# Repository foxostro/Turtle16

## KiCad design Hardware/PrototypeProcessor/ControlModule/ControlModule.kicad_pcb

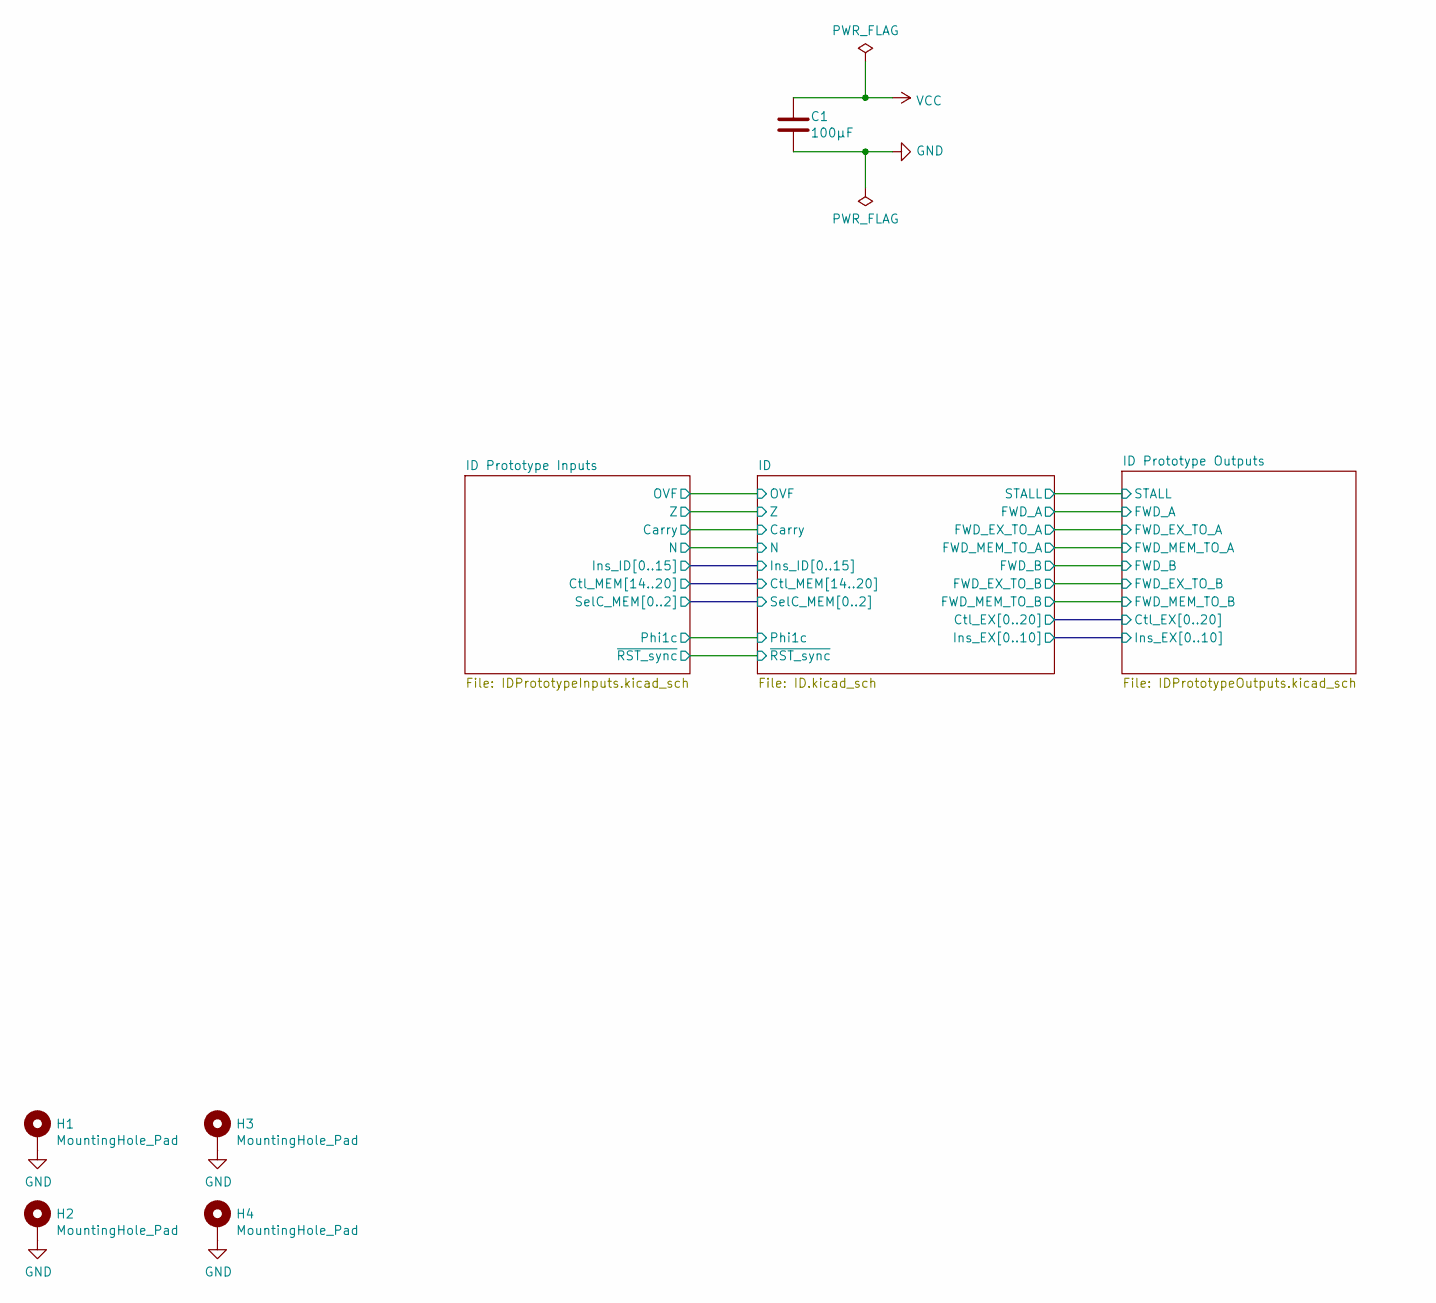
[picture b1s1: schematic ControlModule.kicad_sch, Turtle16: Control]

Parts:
C1: 100µF; C_1206_3216Metric_Pad1.33x1.80mm_HandSolder
H1, H2, H3, H4: MountingHole_Pad; MountingHole_3.2mm_M3_Pad

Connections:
GND: C1.2, H1.1, H2.1, H3.1, H4.1; also elsewhere on the board
VCC: C1.1; also elsewhere on the board

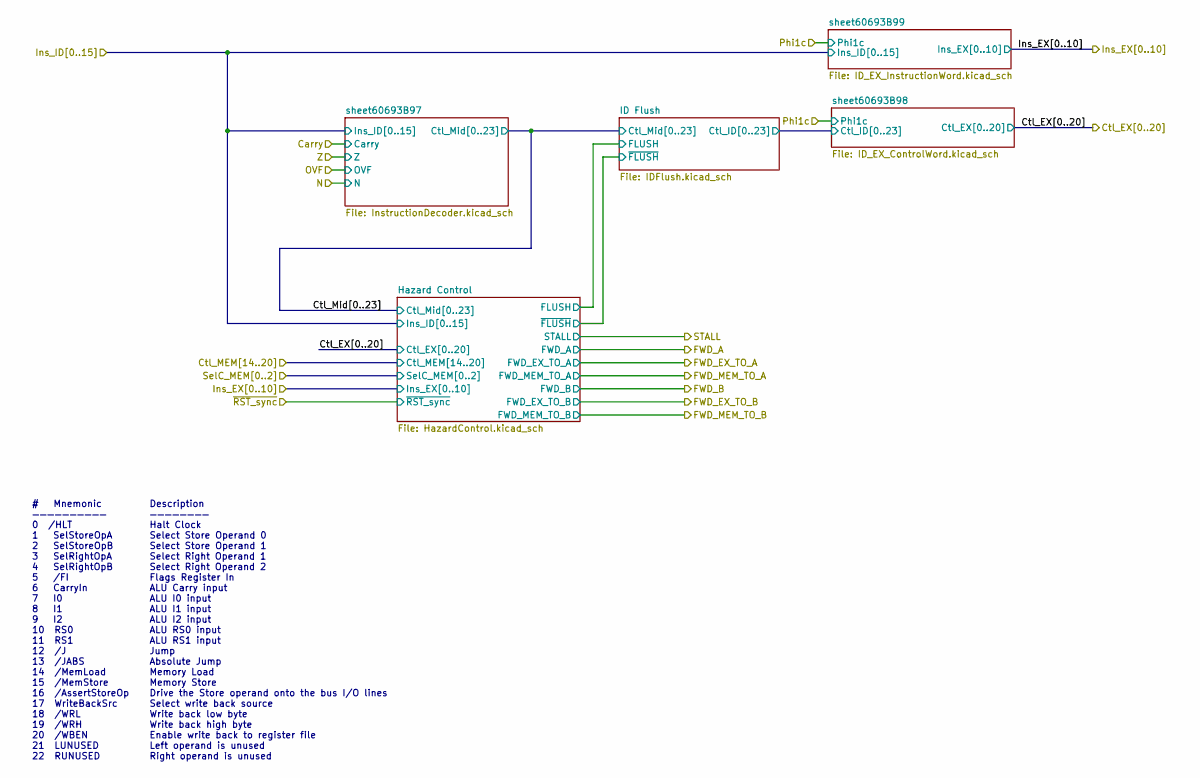
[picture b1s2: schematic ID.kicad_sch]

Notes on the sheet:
Description ———————— Halt Clock Select Store Operand 0 Select Store Operand 1 Select Right Operand 1 Select Right Operand 2 Flags Register In ALU Carry input ALU I0 input ALU I1 input ALU I2 input ALU RS0 input ALU RS1 input Jump Absolute Jump Memory Load Memory Store Drive the Store operand onto t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
# Mnemonic —————————— 0 /HLT 1 SelStoreOpA 2 SelStoreOpB 3 SelRightOpA 4 SelRightOpB 5 /FI 6 CarryIn 7 I0 8 I1 9 I2 10 RS0 11 RS1 12 /J 13 /JABS 14 /MemLoad 15 /MemStore 16 /AssertStoreOp 17 WriteBackSrc 18 /WRL 19 /WRH 20 /WBEN 21 LUNUSED 22 RUNUSED

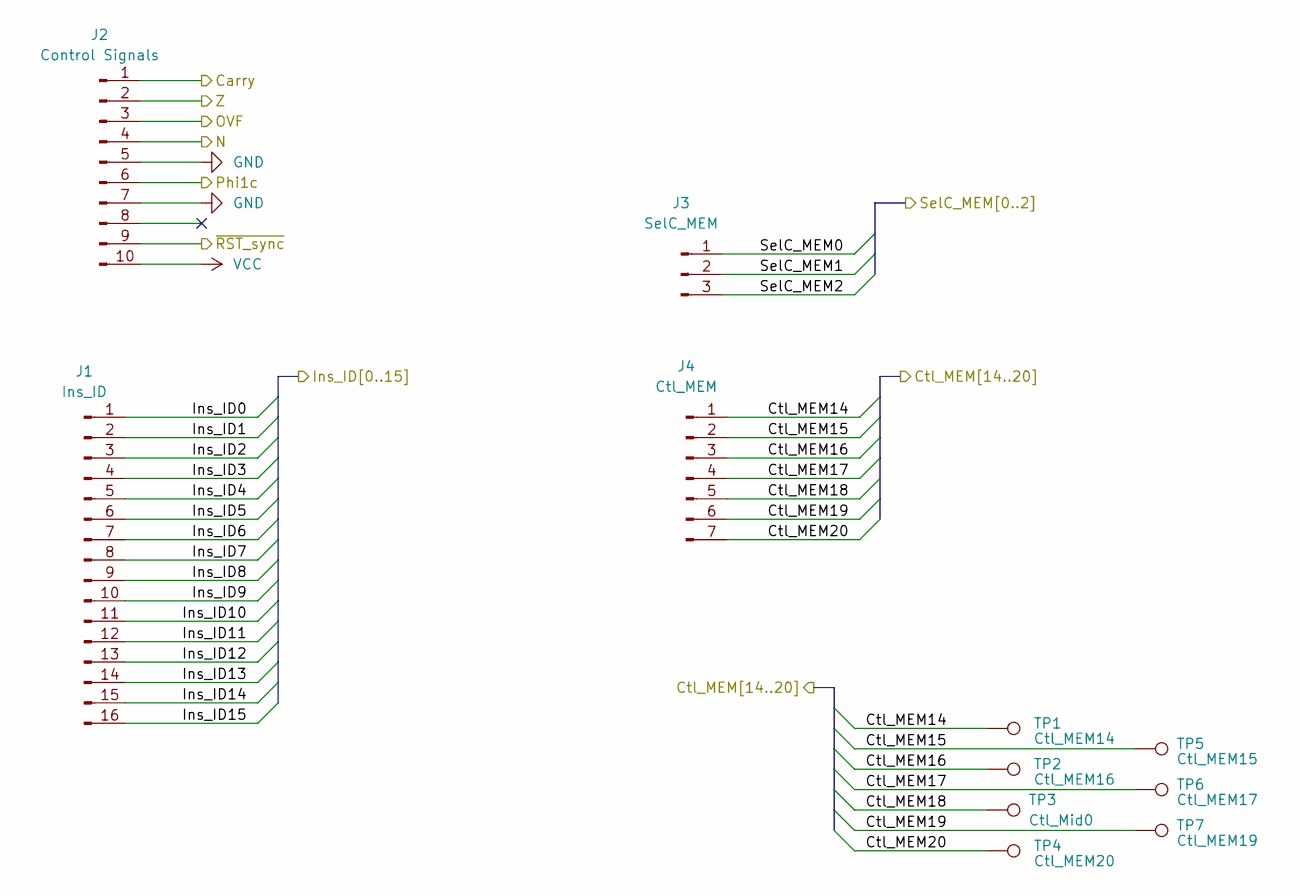
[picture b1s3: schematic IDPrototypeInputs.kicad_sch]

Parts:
J1: Ins_ID; PinHeader_1x16_P2.54mm_Vertical
J2: Control Signals; PinHeader_1x10_P2.54mm_Vertical
J3: SelC_MEM; PinHeader_1x03_P2.54mm_Vertical
J4: Ctl_MEM; PinHeader_1x07_P2.54mm_Vertical
TP1: Ctl_MEM14; TestPoint_Pad_D1.0mm
TP2: Ctl_MEM16; TestPoint_Pad_D1.0mm
TP3: Ctl_Mid0; TestPoint_Pad_D1.0mm
TP4: Ctl_MEM20; TestPoint_Pad_D1.0mm
TP5: Ctl_MEM15; TestPoint_Pad_D1.0mm
TP6: Ctl_MEM17; TestPoint_Pad_D1.0mm
TP7: Ctl_MEM19; TestPoint_Pad_D1.0mm

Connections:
/ID Prototype Inputs/Carry: J2.1; also elsewhere on the board
/ID Prototype Inputs/Ctl_MEM14: J4.1, TP1.1
/ID Prototype Inputs/Ctl_MEM15: J4.2, TP5.1
/ID Prototype Inputs/Ctl_MEM16: J4.3, TP2.1
/ID Prototype Inputs/Ctl_MEM17: J4.4, TP6.1; also elsewhere on the board
/ID Prototype Inputs/Ctl_MEM18: J4.5, TP3.1
/ID Prototype Inputs/Ctl_MEM19: J4.6, TP7.1
/ID Prototype Inputs/Ctl_MEM20: J4.7, TP4.1; also elsewhere on the board
/ID Prototype Inputs/Ins_ID0: J1.1; also elsewhere on the board
/ID Prototype Inputs/Ins_ID1: J1.2; also elsewhere on the board
/ID Prototype Inputs/Ins_ID2: J1.3; also elsewhere on the board
/ID Prototype Inputs/Ins_ID3: J1.4; also elsewhere on the board
/ID Prototype Inputs/Ins_ID4: J1.5; also elsewhere on the board
/ID Prototype Inputs/Ins_ID5: J1.6; also elsewhere on the board
/ID Prototype Inputs/Ins_ID6: J1.7; also elsewhere on the board
/ID Prototype Inputs/Ins_ID7: J1.8; also elsewhere on the board
/ID Prototype Inputs/Ins_ID8: J1.9; also elsewhere on the board
/ID Prototype Inputs/Ins_ID9: J1.10; also elsewhere on the board
/ID Prototype Inputs/Ins_ID10: J1.11; also elsewhere on the board
/ID Prototype Inputs/Ins_ID11: J1.12; also elsewhere on the board
/ID Prototype Inputs/Ins_ID12: J1.13; also elsewhere on the board
/ID Prototype Inputs/Ins_ID13: J1.14; also elsewhere on the board
/ID Prototype Inputs/Ins_ID14: J1.15; also elsewhere on the board
/ID Prototype Inputs/Ins_ID15: J1.16; also elsewhere on the board
/ID Prototype Inputs/N: J2.4; also elsewhere on the board
/ID Prototype Inputs/OVF: J2.3; also elsewhere on the board
/ID Prototype Inputs/Phi1c: J2.6; also elsewhere on the board
/ID Prototype Inputs/SelC_MEM0: J3.1; also elsewhere on the board
/ID Prototype Inputs/SelC_MEM1: J3.2; also elsewhere on the board
/ID Prototype Inputs/SelC_MEM2: J3.3; also elsewhere on the board
/ID Prototype Inputs/Z: J2.2; also elsewhere on the board
/ID Prototype Inputs/~RST_sync: J2.9; also elsewhere on the board
GND: J2.5, J2.7; also elsewhere on the board
VCC: J2.10; also elsewhere on the board

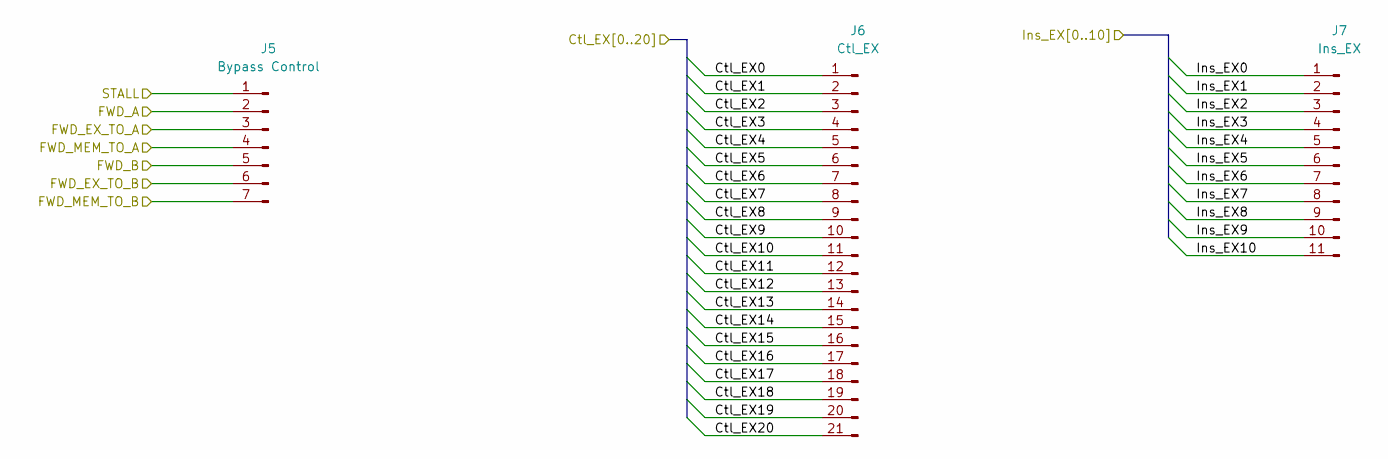
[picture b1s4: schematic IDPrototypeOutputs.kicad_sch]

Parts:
J5: Bypass Control; PinHeader_1x07_P2.54mm_Vertical
J6: Ctl_EX; PinHeader_1x21_P2.54mm_Vertical
J7: Ins_EX; PinHeader_1x11_P2.54mm_Vertical

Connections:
/ID Prototype Outputs/FWD_A: J5.2; also elsewhere on the board
/ID Prototype Outputs/FWD_B: J5.5; also elsewhere on the board
/ID Prototype Outputs/FWD_EX_TO_A: J5.3; also elsewhere on the board
/ID Prototype Outputs/FWD_EX_TO_B: J5.6; also elsewhere on the board
/ID Prototype Outputs/FWD_MEM_TO_A: J5.4; also elsewhere on the board
/ID Prototype Outputs/FWD_MEM_TO_B: J5.7; also elsewhere on the board
/ID Prototype Outputs/Ins_EX0: J7.1; also elsewhere on the board
/ID Prototype Outputs/Ins_EX1: J7.2; also elsewhere on the board
/ID Prototype Outputs/Ins_EX2: J7.3; also elsewhere on the board
/ID Prototype Outputs/Ins_EX3: J7.4; also elsewhere on the board
/ID Prototype Outputs/Ins_EX4: J7.5; also elsewhere on the board
/ID Prototype Outputs/Ins_EX5: J7.6; also elsewhere on the board
/ID Prototype Outputs/Ins_EX6: J7.7; also elsewhere on the board
/ID Prototype Outputs/Ins_EX7: J7.8; also elsewhere on the board
/ID Prototype Outputs/Ins_EX8: J7.9; also elsewhere on the board
/ID Prototype Outputs/Ins_EX9: J7.10; also elsewhere on the board
/ID Prototype Outputs/Ins_EX10: J7.11; also elsewhere on the board
/ID/Ctl_EX0: J6.1; also elsewhere on the board
/ID/Ctl_EX1: J6.2; also elsewhere on the board
/ID/Ctl_EX2: J6.3; also elsewhere on the board
/ID/Ctl_EX3: J6.4; also elsewhere on the board
/ID/Ctl_EX4: J6.5; also elsewhere on the board
/ID/Ctl_EX5: J6.6; also elsewhere on the board
/ID/Ctl_EX6: J6.7; also elsewhere on the board
/ID/Ctl_EX7: J6.8; also elsewhere on the board
/ID/Ctl_EX8: J6.9; also elsewhere on the board
/ID/Ctl_EX9: J6.10; also elsewhere on the board
/ID/Ctl_EX10: J6.11; also elsewhere on the board
/ID/Ctl_EX11: J6.12; also elsewhere on the board
/ID/Ctl_EX12: J6.13; also elsewhere on the board
/ID/Ctl_EX13: J6.14; also elsewhere on the board
/ID/Ctl_EX14: J6.15; also elsewhere on the board
/ID/Ctl_EX15: J6.16; also elsewhere on the board
/ID/Ctl_EX16: J6.17; also elsewhere on the board
/ID/Ctl_EX17: J6.18; also elsewhere on the board
/ID/Ctl_EX18: J6.19; also elsewhere on the board
/ID/Ctl_EX19: J6.20; also elsewhere on the board
/ID/Ctl_EX20: J6.21; also elsewhere on the board
/ID/Hazard Control/STALL: J5.1; also elsewhere on the board

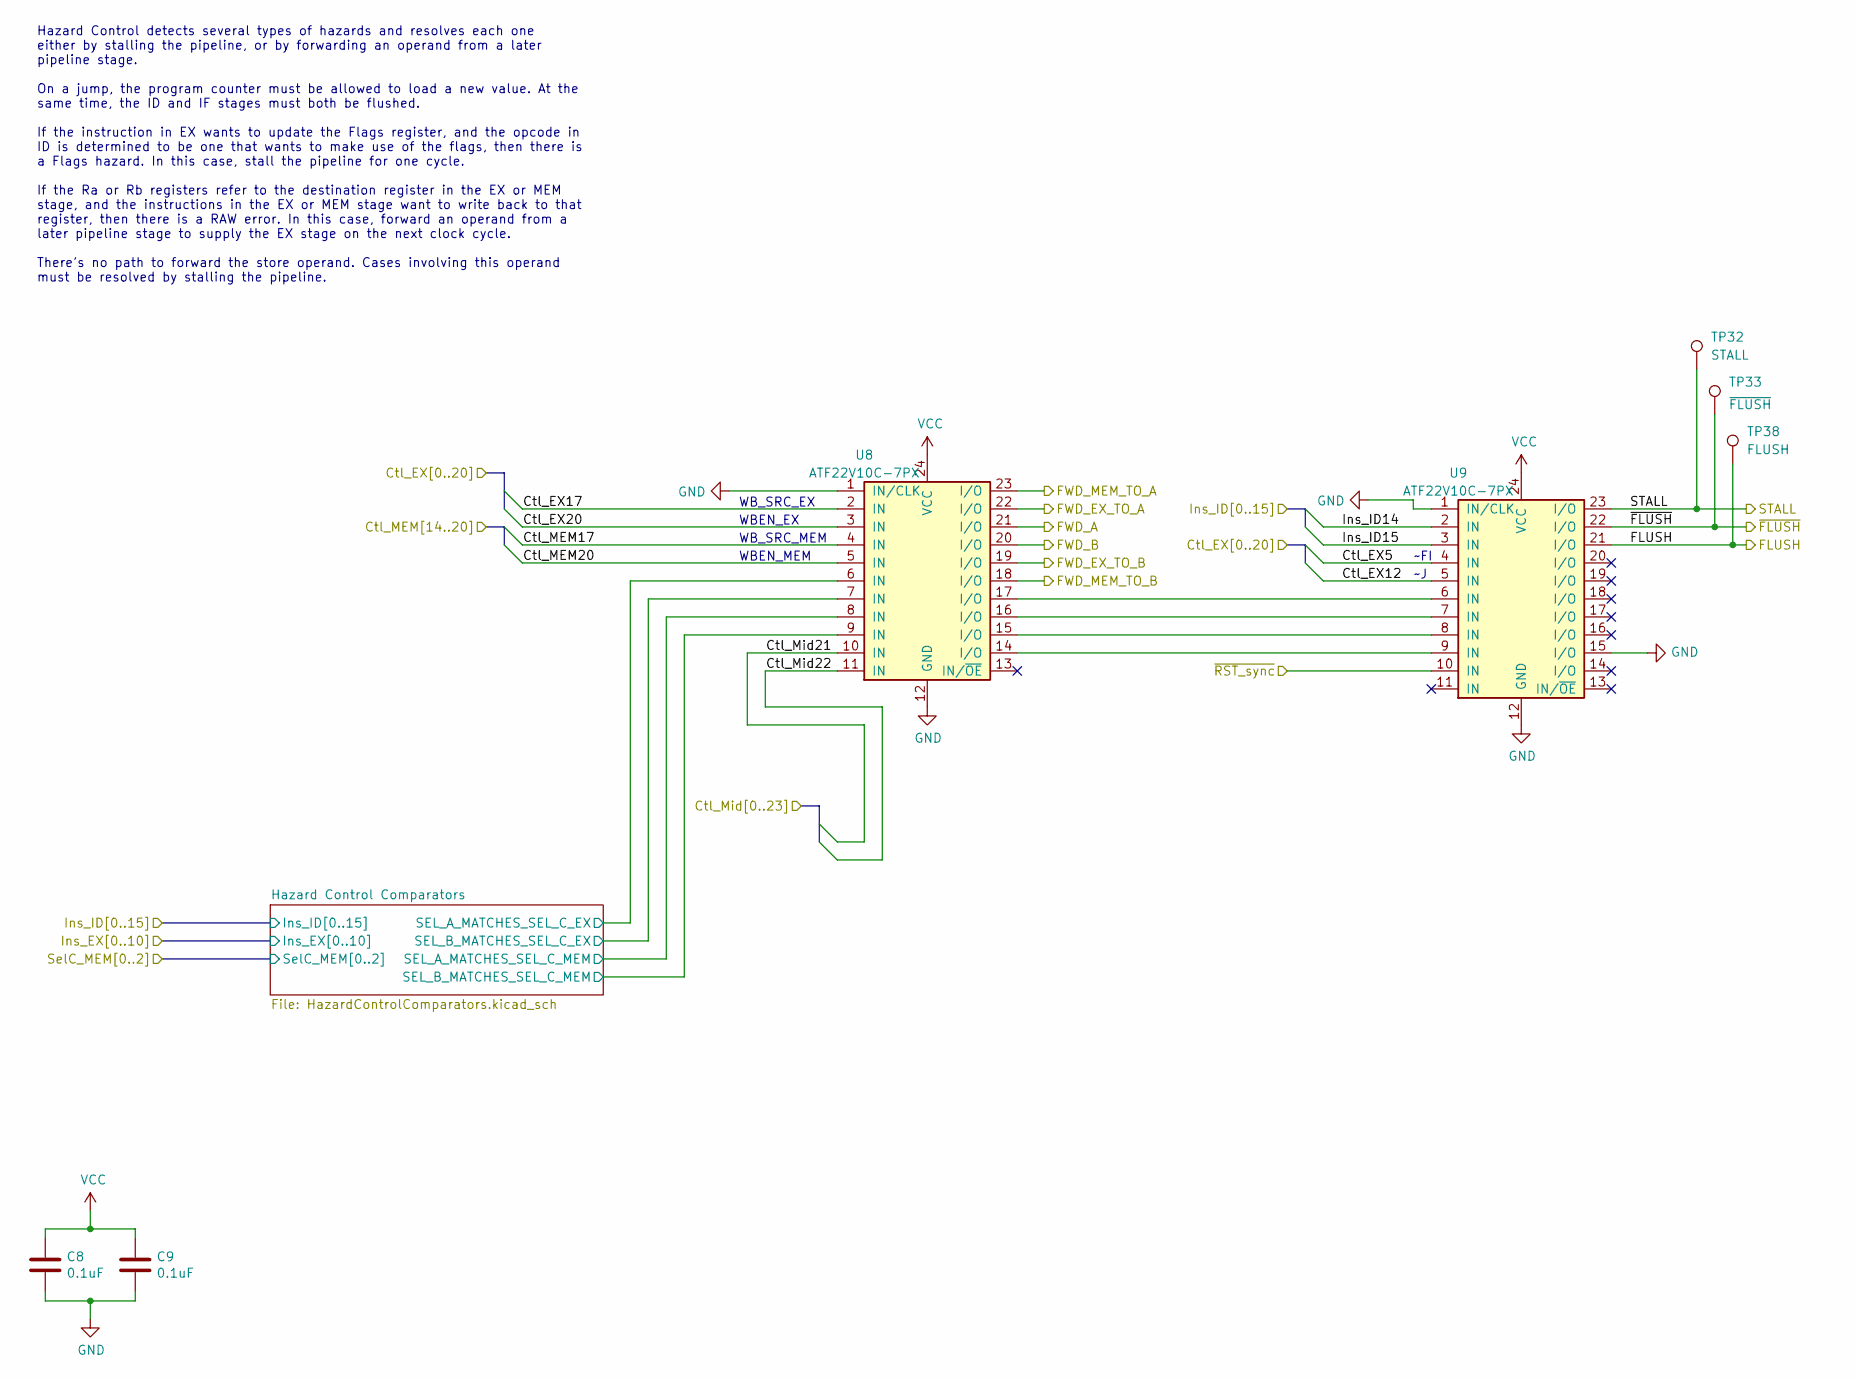
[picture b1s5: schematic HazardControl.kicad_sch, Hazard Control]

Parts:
C8, C9: 0.1uF; C_0603_1608Metric_Pad1.08x0.95mm_HandSolder
TP32: STALL; TestPoint_Pad_D1.0mm
TP33: ~{FLUSH}; TestPoint_Pad_D1.0mm
TP38: FLUSH; TestPoint_Pad_D1.0mm
U8, U9: ATF22V10C-7PX; DIP-24_W7.62mm_Socket

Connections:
/ID Prototype Inputs/Ctl_MEM17: U8.4 (IN); also elsewhere on the board
/ID Prototype Inputs/Ctl_MEM20: U8.5 (IN); also elsewhere on the board
/ID Prototype Inputs/Ins_ID14: U9.2 (IN); also elsewhere on the board
/ID Prototype Inputs/Ins_ID15: U9.3 (IN); also elsewhere on the board
/ID Prototype Inputs/~RST_sync: U9.10 (IN); also elsewhere on the board
/ID Prototype Outputs/FWD_A: U8.21 (I/O); also elsewhere on the board
/ID Prototype Outputs/FWD_B: U8.20 (I/O); also elsewhere on the board
/ID Prototype Outputs/FWD_EX_TO_A: U8.22 (I/O); also elsewhere on the board
/ID Prototype Outputs/FWD_EX_TO_B: U8.19 (I/O); also elsewhere on the board
/ID Prototype Outputs/FWD_MEM_TO_A: U8.23 (I/O); also elsewhere on the board
/ID Prototype Outputs/FWD_MEM_TO_B: U8.18 (I/O); also elsewhere on the board
/ID/Ctl_EX5: U9.4 (IN); also elsewhere on the board
/ID/Ctl_EX12: U9.5 (IN); also elsewhere on the board
/ID/Ctl_EX17: U8.2 (IN); also elsewhere on the board
/ID/Ctl_EX20: U8.3 (IN); also elsewhere on the board
/ID/Ctl_Mid21: U8.10 (IN); also elsewhere on the board
/ID/Ctl_Mid22: U8.11 (IN); also elsewhere on the board
/ID/Hazard Control/FLUSH: TP38.1, U9.21 (I/O); also elsewhere on the board
/ID/Hazard Control/Hazard Control Comparators/SEL_A_MATCHES_SEL_C_EX: U8.6 (IN); also elsewhere on the board
/ID/Hazard Control/Hazard Control Comparators/SEL_A_MATCHES_SEL_C_MEM: U8.8 (IN); also elsewhere on the board
/ID/Hazard Control/Hazard Control Comparators/SEL_B_MATCHES_SEL_C_EX: U8.7 (IN); also elsewhere on the board
/ID/Hazard Control/Hazard Control Comparators/SEL_B_MATCHES_SEL_C_MEM: U8.9 (IN); also elsewhere on the board
/ID/Hazard Control/STALL: TP32.1, U9.23 (I/O); also elsewhere on the board
/ID/Hazard Control/~FLUSH: TP33.1, U9.22 (I/O); also elsewhere on the board
GND: C8.2, C9.2, U8.1 (IN/CLK), U8.12 (GND), U9.1 (IN/CLK), U9.12 (GND), U9.15 (I/O); also elsewhere on the board
unnamed: U8.14 (I/O), U9.9 (IN)
unnamed: U8.15 (I/O), U9.8 (IN)
unnamed: U8.16 (I/O), U9.7 (IN)
unnamed: U8.17 (I/O), U9.6 (IN)
VCC: C8.1, C9.1, U8.24 (VCC), U9.24 (VCC); also elsewhere on the board

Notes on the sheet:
Hazard Control detects several types of hazards and resolves each one either by stalling the pipeline, or by forwarding an operand from a later pipeline stage. On a jump, the program counter must be allowed to load a new value. At the same time, the ID and IF stages must both be flushed. If the ins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
WBEN_EX
WBEN_MEM
WB_SRC_EX
~FI
WB_SRC_MEM

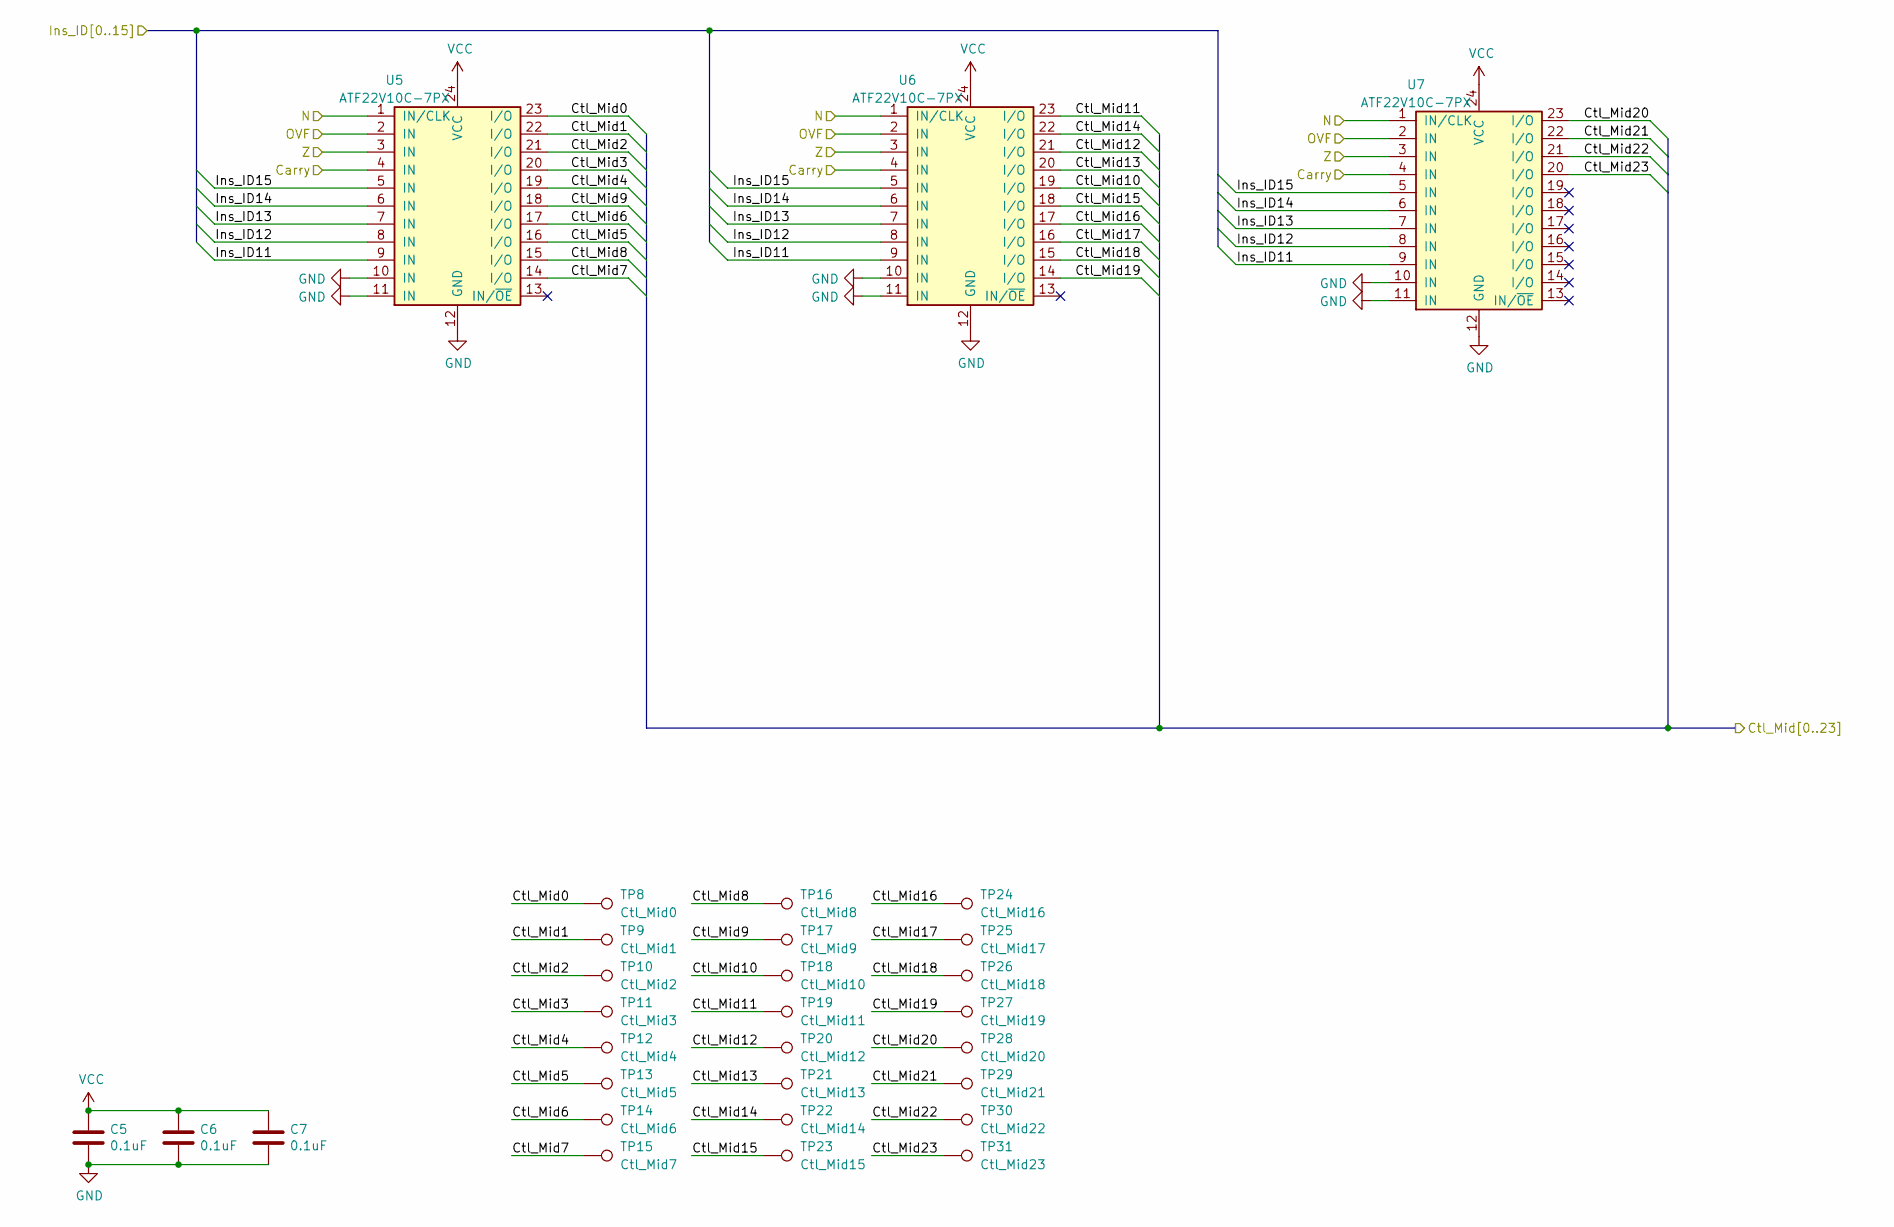
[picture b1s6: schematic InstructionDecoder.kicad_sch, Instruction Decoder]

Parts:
C5, C6, C7: 0.1uF; C_0603_1608Metric_Pad1.08x0.95mm_HandSolder
TP8: Ctl_Mid0; TestPoint_Pad_D1.0mm
TP9: Ctl_Mid1; TestPoint_Pad_D1.0mm
TP10: Ctl_Mid2; TestPoint_Pad_D1.0mm
TP11: Ctl_Mid3; TestPoint_Pad_D1.0mm
TP12: Ctl_Mid4; TestPoint_Pad_D1.0mm
TP13: Ctl_Mid5; TestPoint_Pad_D1.0mm
TP14: Ctl_Mid6; TestPoint_Pad_D1.0mm
TP15: Ctl_Mid7; TestPoint_Pad_D1.0mm
TP16: Ctl_Mid8; TestPoint_Pad_D1.0mm
TP17: Ctl_Mid9; TestPoint_Pad_D1.0mm
TP18: Ctl_Mid10; TestPoint_Pad_D1.0mm
TP19: Ctl_Mid11; TestPoint_Pad_D1.0mm
TP20: Ctl_Mid12; TestPoint_Pad_D1.0mm
TP21: Ctl_Mid13; TestPoint_Pad_D1.0mm
TP22: Ctl_Mid14; TestPoint_Pad_D1.0mm
TP23: Ctl_Mid15; TestPoint_Pad_D1.0mm
TP24: Ctl_Mid16; TestPoint_Pad_D1.0mm
TP25: Ctl_Mid17; TestPoint_Pad_D1.0mm
TP26: Ctl_Mid18; TestPoint_Pad_D1.0mm
TP27: Ctl_Mid19; TestPoint_Pad_D1.0mm
TP28: Ctl_Mid20; TestPoint_Pad_D1.0mm
TP29: Ctl_Mid21; TestPoint_Pad_D1.0mm
TP30: Ctl_Mid22; TestPoint_Pad_D1.0mm
TP31: Ctl_Mid23; TestPoint_Pad_D1.0mm
U5, U6, U7: ATF22V10C-7PX; DIP-24_W7.62mm_Socket

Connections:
/ID Prototype Inputs/Carry: U5.4 (IN), U6.4 (IN), U7.4 (IN); also elsewhere on the board
/ID Prototype Inputs/Ins_ID11: U5.9 (IN), U6.9 (IN), U7.9 (IN); also elsewhere on the board
/ID Prototype Inputs/Ins_ID12: U5.8 (IN), U6.8 (IN), U7.8 (IN); also elsewhere on the board
/ID Prototype Inputs/Ins_ID13: U5.7 (IN), U6.7 (IN), U7.7 (IN); also elsewhere on the board
/ID Prototype Inputs/Ins_ID14: U5.6 (IN), U6.6 (IN), U7.6 (IN); also elsewhere on the board
/ID Prototype Inputs/Ins_ID15: U5.5 (IN), U6.5 (IN), U7.5 (IN); also elsewhere on the board
/ID Prototype Inputs/N: U5.1 (IN/CLK), U6.1 (IN/CLK), U7.1 (IN/CLK); also elsewhere on the board
/ID Prototype Inputs/OVF: U5.2 (IN), U6.2 (IN), U7.2 (IN); also elsewhere on the board
/ID Prototype Inputs/Z: U5.3 (IN), U6.3 (IN), U7.3 (IN); also elsewhere on the board
/ID/Ctl_Mid0: TP8.1, U5.23 (I/O); also elsewhere on the board
/ID/Ctl_Mid1: TP9.1, U5.22 (I/O); also elsewhere on the board
/ID/Ctl_Mid2: TP10.1, U5.21 (I/O); also elsewhere on the board
/ID/Ctl_Mid3: TP11.1, U5.20 (I/O); also elsewhere on the board
/ID/Ctl_Mid4: TP12.1, U5.19 (I/O); also elsewhere on the board
/ID/Ctl_Mid5: TP13.1, U5.16 (I/O); also elsewhere on the board
/ID/Ctl_Mid6: TP14.1, U5.17 (I/O); also elsewhere on the board
/ID/Ctl_Mid7: TP15.1, U5.14 (I/O); also elsewhere on the board
/ID/Ctl_Mid8: TP16.1, U5.15 (I/O); also elsewhere on the board
/ID/Ctl_Mid9: TP17.1, U5.18 (I/O); also elsewhere on the board
/ID/Ctl_Mid10: TP18.1, U6.19 (I/O); also elsewhere on the board
/ID/Ctl_Mid11: TP19.1, U6.23 (I/O); also elsewhere on the board
/ID/Ctl_Mid12: TP20.1, U6.21 (I/O); also elsewhere on the board
/ID/Ctl_Mid13: TP21.1, U6.20 (I/O); also elsewhere on the board
/ID/Ctl_Mid14: TP22.1, U6.22 (I/O); also elsewhere on the board
/ID/Ctl_Mid15: TP23.1, U6.18 (I/O); also elsewhere on the board
/ID/Ctl_Mid16: TP24.1, U6.17 (I/O); also elsewhere on the board
/ID/Ctl_Mid17: TP25.1, U6.16 (I/O); also elsewhere on the board
/ID/Ctl_Mid18: TP26.1, U6.15 (I/O); also elsewhere on the board
/ID/Ctl_Mid19: TP27.1, U6.14 (I/O); also elsewhere on the board
/ID/Ctl_Mid20: TP28.1, U7.23 (I/O); also elsewhere on the board
/ID/Ctl_Mid21: TP29.1, U7.22 (I/O); also elsewhere on the board
/ID/Ctl_Mid22: TP30.1, U7.21 (I/O); also elsewhere on the board
/ID/Ctl_Mid23: TP31.1, U7.20 (I/O); also elsewhere on the board
GND: C5.2, C6.2, C7.2, U5.10 (IN), U5.11 (IN), U5.12 (GND), U6.10 (IN), U6.11 (IN), U6.12 (GND), U7.10 (IN), U7.11 (IN), U7.12 (GND); also elsewhere on the board
VCC: C5.1, C6.1, C7.1, U5.24 (VCC), U6.24 (VCC), U7.24 (VCC); also elsewhere on the board

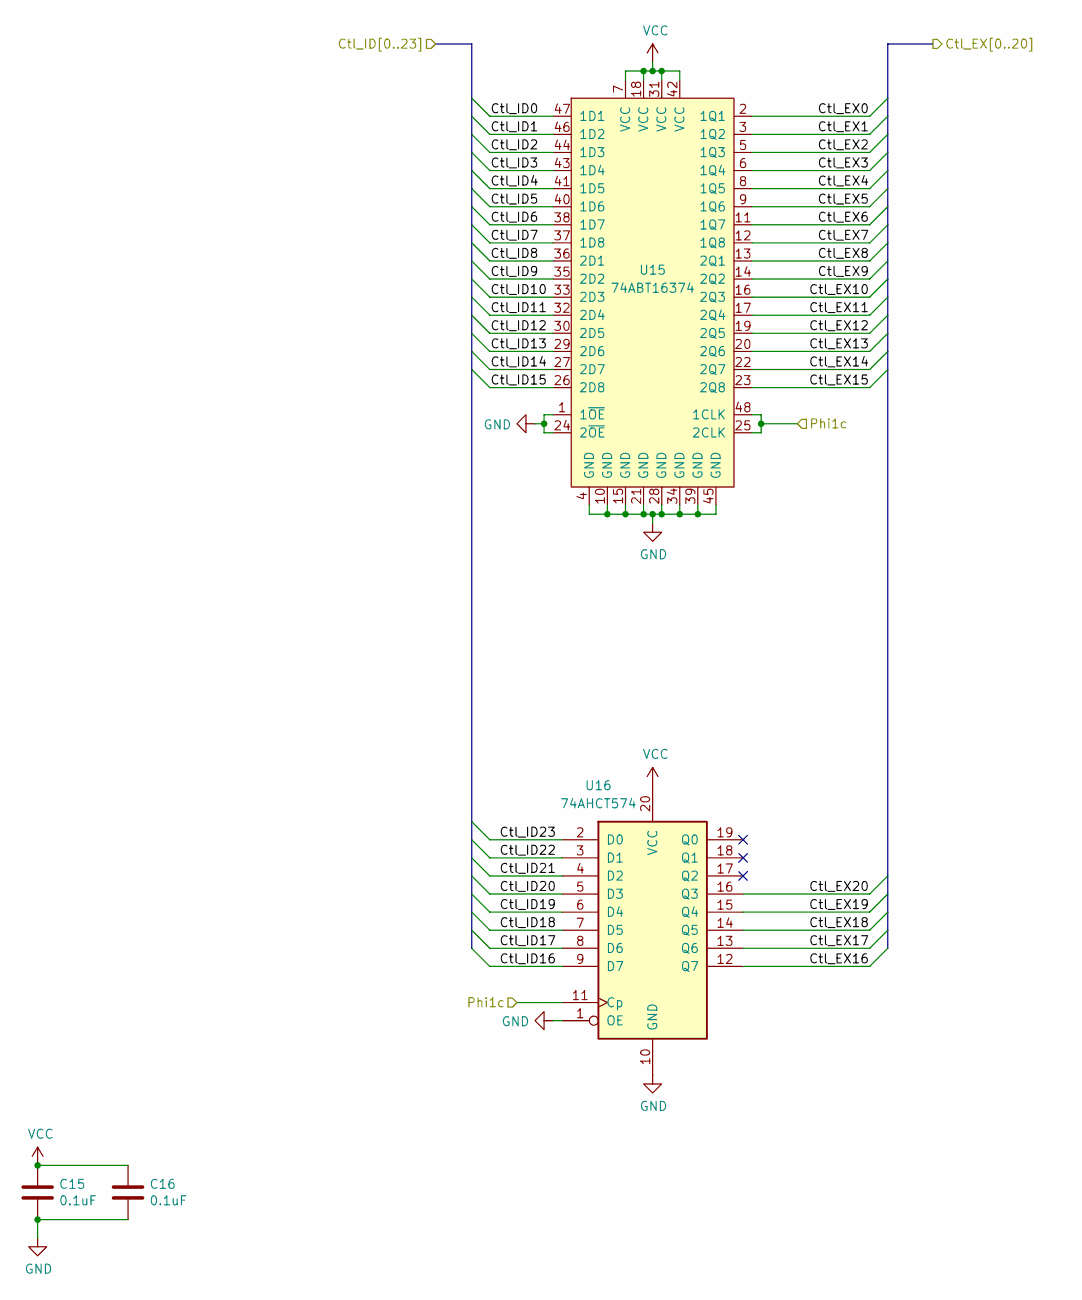
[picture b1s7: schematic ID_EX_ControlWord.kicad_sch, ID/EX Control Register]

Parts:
C15, C16: 0.1uF; C_0603_1608Metric_Pad1.08x0.95mm_HandSolder
U15: 74ABT16374; TSSOP-48_6.1x12.5mm_P0.5mm
U16: 74AHCT574; TSSOP-20_4.4x6.5mm_P0.65mm

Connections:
/ID Prototype Inputs/Phi1c: U15.25 (2CLK), U15.48 (1CLK), U16.11 (Cp); also elsewhere on the board
/ID/Ctl_EX0: U15.2 (1Q1); also elsewhere on the board
/ID/Ctl_EX1: U15.3 (1Q2); also elsewhere on the board
/ID/Ctl_EX2: U15.5 (1Q3); also elsewhere on the board
/ID/Ctl_EX3: U15.6 (1Q4); also elsewhere on the board
/ID/Ctl_EX4: U15.8 (1Q5); also elsewhere on the board
/ID/Ctl_EX5: U15.9 (1Q6); also elsewhere on the board
/ID/Ctl_EX6: U15.11 (1Q7); also elsewhere on the board
/ID/Ctl_EX7: U15.12 (1Q8); also elsewhere on the board
/ID/Ctl_EX8: U15.13 (2Q1); also elsewhere on the board
/ID/Ctl_EX9: U15.14 (2Q2); also elsewhere on the board
/ID/Ctl_EX10: U15.16 (2Q3); also elsewhere on the board
/ID/Ctl_EX11: U15.17 (2Q4); also elsewhere on the board
/ID/Ctl_EX12: U15.19 (2Q5); also elsewhere on the board
/ID/Ctl_EX13: U15.20 (2Q6); also elsewhere on the board
/ID/Ctl_EX14: U15.22 (2Q7); also elsewhere on the board
/ID/Ctl_EX15: U15.23 (2Q8); also elsewhere on the board
/ID/Ctl_EX16: U16.12 (Q7); also elsewhere on the board
/ID/Ctl_EX17: U16.13 (Q6); also elsewhere on the board
/ID/Ctl_EX18: U16.14 (Q5); also elsewhere on the board
/ID/Ctl_EX19: U16.15 (Q4); also elsewhere on the board
/ID/Ctl_EX20: U16.16 (Q3); also elsewhere on the board
/ID/ID Flush/Ctl_ID0: U15.47 (1D1); also elsewhere on the board
/ID/ID Flush/Ctl_ID1: U15.46 (1D2); also elsewhere on the board
/ID/ID Flush/Ctl_ID2: U15.44 (1D3); also elsewhere on the board
/ID/ID Flush/Ctl_ID3: U15.43 (1D4); also elsewhere on the board
/ID/ID Flush/Ctl_ID4: U15.41 (1D5); also elsewhere on the board
/ID/ID Flush/Ctl_ID5: U15.40 (1D6); also elsewhere on the board
/ID/ID Flush/Ctl_ID6: U15.38 (1D7); also elsewhere on the board
/ID/ID Flush/Ctl_ID7: U15.37 (1D8); also elsewhere on the board
/ID/ID Flush/Ctl_ID8: U15.36 (2D1); also elsewhere on the board
/ID/ID Flush/Ctl_ID9: U15.35 (2D2); also elsewhere on the board
/ID/ID Flush/Ctl_ID10: U15.33 (2D3); also elsewhere on the board
/ID/ID Flush/Ctl_ID11: U15.32 (2D4); also elsewhere on the board
/ID/ID Flush/Ctl_ID12: U15.30 (2D5); also elsewhere on the board
/ID/ID Flush/Ctl_ID13: U15.29 (2D6); also elsewhere on the board
/ID/ID Flush/Ctl_ID14: U15.27 (2D7); also elsewhere on the board
/ID/ID Flush/Ctl_ID15: U15.26 (2D8); also elsewhere on the board
/ID/ID Flush/Ctl_ID16: U16.9 (D7); also elsewhere on the board
/ID/ID Flush/Ctl_ID17: U16.8 (D6); also elsewhere on the board
/ID/ID Flush/Ctl_ID18: U16.7 (D5); also elsewhere on the board
/ID/ID Flush/Ctl_ID19: U16.6 (D4); also elsewhere on the board
/ID/ID Flush/Ctl_ID20: U16.5 (D3); also elsewhere on the board
/ID/ID Flush/Ctl_ID21: U16.4 (D2); also elsewhere on the board
/ID/ID Flush/Ctl_ID22: U16.3 (D1); also elsewhere on the board
/ID/ID Flush/Ctl_ID23: U16.2 (D0); also elsewhere on the board
GND: C15.2, C16.2, U15.1 (1~OE), U15.4 (GND), U15.10 (GND), U15.15 (GND), U15.21 (GND), U15.24 (2~OE), U15.28 (GND), U15.34 (GND), U15.39 (GND), U15.45 (GND), U16.1 (OE), U16.10 (GND); also elsewhere on the board
VCC: C15.1, C16.1, U15.7 (VCC), U15.18 (VCC), U15.31 (VCC), U15.42 (VCC), U16.20 (VCC); also elsewhere on the board

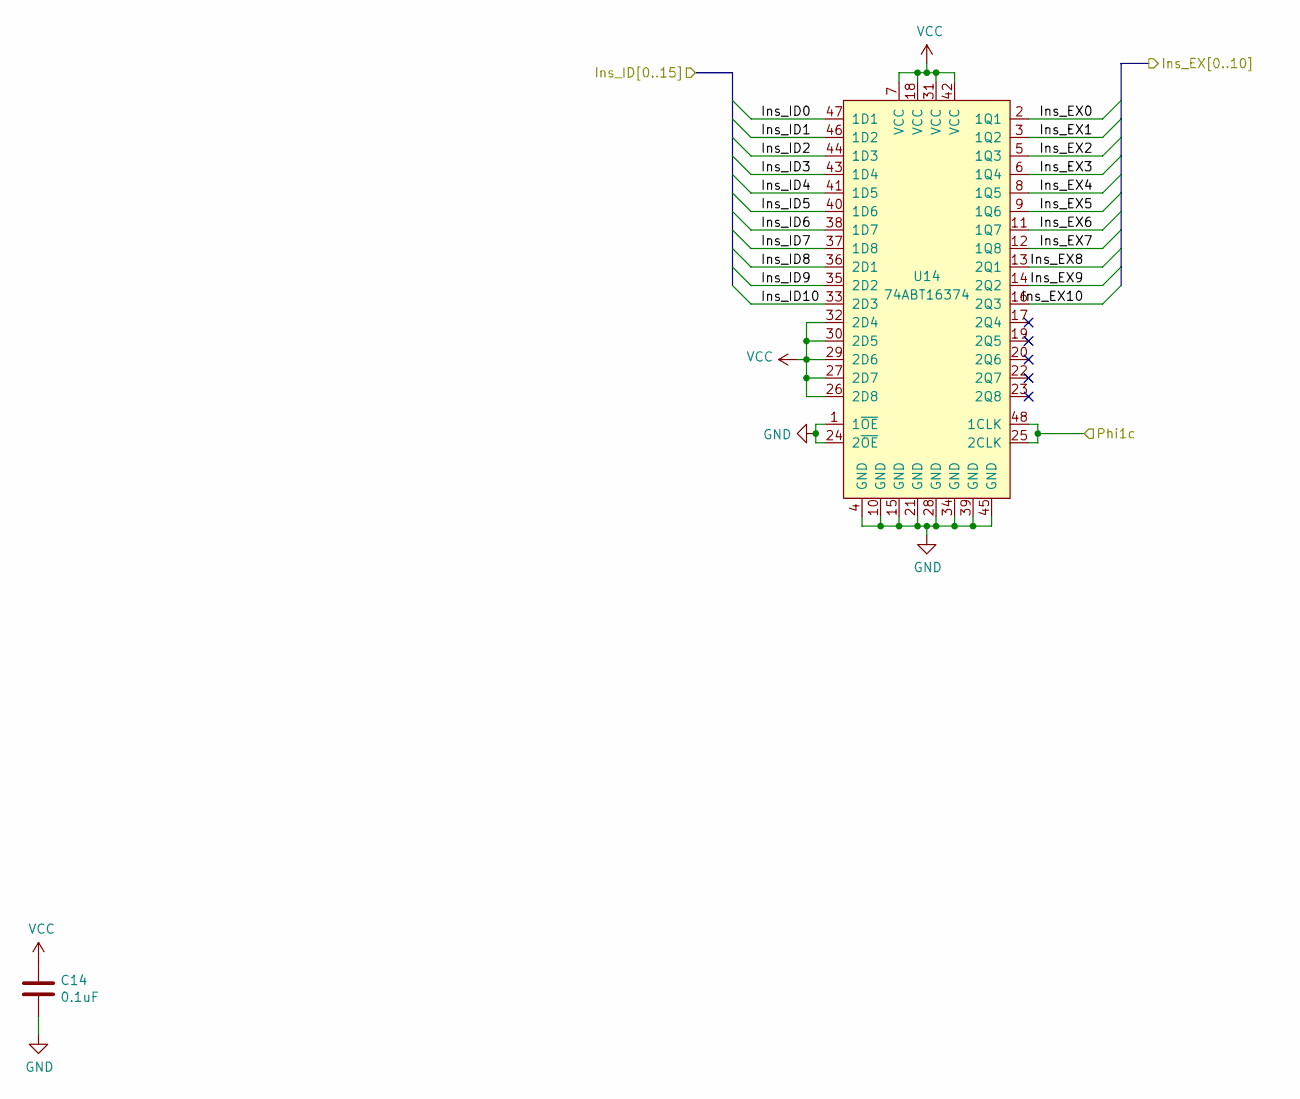
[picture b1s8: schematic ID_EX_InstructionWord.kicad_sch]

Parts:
C14: 0.1uF; C_0603_1608Metric_Pad1.08x0.95mm_HandSolder
U14: 74ABT16374; TSSOP-48_6.1x12.5mm_P0.5mm

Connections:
/ID Prototype Inputs/Ins_ID0: U14.47 (1D1); also elsewhere on the board
/ID Prototype Inputs/Ins_ID1: U14.46 (1D2); also elsewhere on the board
/ID Prototype Inputs/Ins_ID2: U14.44 (1D3); also elsewhere on the board
/ID Prototype Inputs/Ins_ID3: U14.43 (1D4); also elsewhere on the board
/ID Prototype Inputs/Ins_ID4: U14.41 (1D5); also elsewhere on the board
/ID Prototype Inputs/Ins_ID5: U14.40 (1D6); also elsewhere on the board
/ID Prototype Inputs/Ins_ID6: U14.38 (1D7); also elsewhere on the board
/ID Prototype Inputs/Ins_ID7: U14.37 (1D8); also elsewhere on the board
/ID Prototype Inputs/Ins_ID8: U14.36 (2D1); also elsewhere on the board
/ID Prototype Inputs/Ins_ID9: U14.35 (2D2); also elsewhere on the board
/ID Prototype Inputs/Ins_ID10: U14.33 (2D3); also elsewhere on the board
/ID Prototype Inputs/Phi1c: U14.25 (2CLK), U14.48 (1CLK); also elsewhere on the board
/ID Prototype Outputs/Ins_EX0: U14.2 (1Q1); also elsewhere on the board
/ID Prototype Outputs/Ins_EX1: U14.3 (1Q2); also elsewhere on the board
/ID Prototype Outputs/Ins_EX2: U14.5 (1Q3); also elsewhere on the board
/ID Prototype Outputs/Ins_EX3: U14.6 (1Q4); also elsewhere on the board
/ID Prototype Outputs/Ins_EX4: U14.8 (1Q5); also elsewhere on the board
/ID Prototype Outputs/Ins_EX5: U14.9 (1Q6); also elsewhere on the board
/ID Prototype Outputs/Ins_EX6: U14.11 (1Q7); also elsewhere on the board
/ID Prototype Outputs/Ins_EX7: U14.12 (1Q8); also elsewhere on the board
/ID Prototype Outputs/Ins_EX8: U14.13 (2Q1); also elsewhere on the board
/ID Prototype Outputs/Ins_EX9: U14.14 (2Q2); also elsewhere on the board
/ID Prototype Outputs/Ins_EX10: U14.16 (2Q3); also elsewhere on the board
GND: C14.2, U14.1 (1~OE), U14.4 (GND), U14.10 (GND), U14.15 (GND), U14.21 (GND), U14.24 (2~OE), U14.28 (GND), U14.34 (GND), U14.39 (GND), U14.45 (GND); also elsewhere on the board
VCC: C14.1, U14.7 (VCC), U14.18 (VCC), U14.26 (2D8), U14.27 (2D7), U14.29 (2D6), U14.30 (2D5), U14.31 (VCC), U14.32 (2D4), U14.42 (VCC); also elsewhere on the board

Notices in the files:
Hardware/PrototypeProcessor/ControlModule/ControlModule.kicad_pcb:
Copyright © 2022-2023 Andrew Fox
Hardware/PrototypeProcessor/ControlModuleTestFixture/ControlModuleTestFixture.kicad_pcb:
Copyright © 2023
Hardware/PrototypeProcessor/EXModule/EXModule.kicad_pcb:
Copyright © 2022 Andrew Fox
Hardware/PrototypeProcessor/MEMModule/MEMModule.kicad_pcb:
Copyright © 2023 Andrew Fox
Hardware/PrototypeProcessor/ProgramCounterPrototype/ProgramCounterPrototype.kicad_pcb:
Copyright © 2021 Andrew Fox
